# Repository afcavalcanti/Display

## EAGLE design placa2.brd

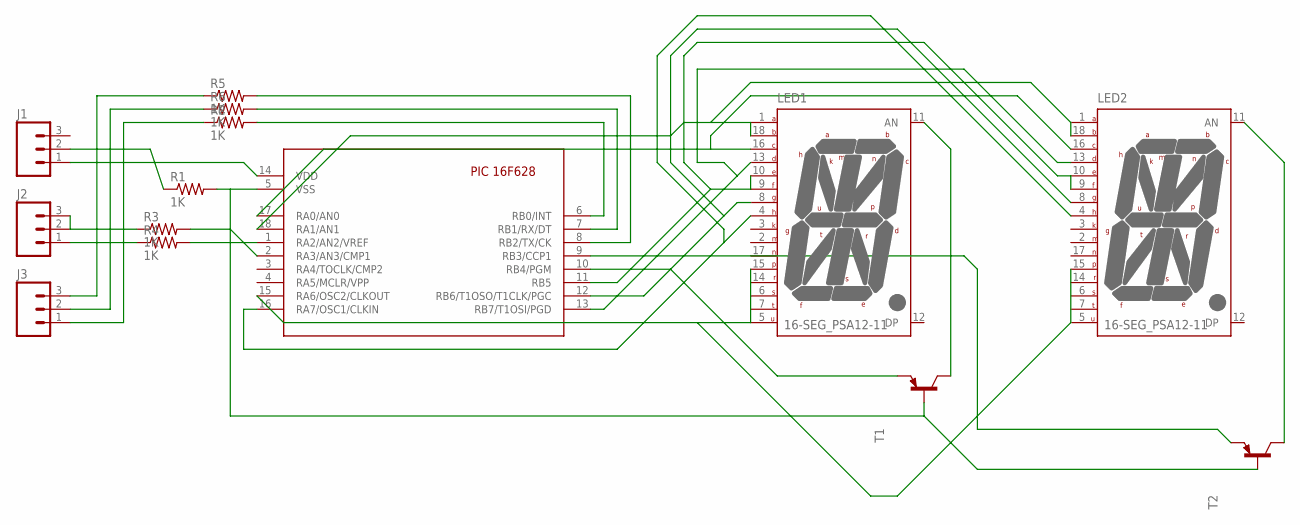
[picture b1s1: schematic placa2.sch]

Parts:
J1, J2, J3: M03-SCREW-5MM; SCREWTERMINAL-5MM-3
LED1, LED2: 16-SEG_PSA12-11; PSA12-11
R1, R2, R3, R4, R5, R6: 1K; AXIAL-0.3
T1, T2: BC558B-PNP-TO92-EBC; TO92-EBC
U$1: 16F628; PIC16F628-18-LEAD-PDIP

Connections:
unnamed: J1.1, U$1.14 (VDD)
unnamed: J1.2, R1.P$1 (1)
unnamed: J2.1, R4.P$1 (1)
unnamed: R1.P$2 (2), T1.B, T2.B, U$1.5 (VSS)
unnamed: J2.3, R3.P$1 (1)
unnamed: J3.3, R5.P$1 (1)
unnamed: R2.P$2 (2), U$1.6 (RB0/INT)
unnamed: R6.P$2 (2), U$1.7 (RB1/RX/DT)
unnamed: R5.P$2 (2), U$1.8 (RB2/TX/CK)
unnamed: LED1.1 (A), LED1.18 (B), LED2.1 (A), LED2.18 (B), U$1.18 (RA1/AN1)
unnamed: LED1.4 (H), LED2.4 (H), U$1.16 (RA7/OSC1/CLKIN)
unnamed: LED1.11 (AN), T1.C
unnamed: LED1.16 (C), LED2.16 (C), U$1.17 (RA0/AN0)
unnamed: J3.2, R6.P$1 (1)
unnamed: LED2.11 (AN), T2.C
unnamed: J3.1, R2.P$1 (1)
unnamed: LED1.13 (D), LED2.13 (D), U$1.13 (RB7/T1OSI/PGD)
unnamed: LED1.8 (G), LED2.8 (G), U$1.12 (RB6/T1OSO/T1CLK/PGC)
unnamed: T1.E, U$1.10 (RB4/PGM)
unnamed: T2.E, U$1.9 (RB3/CCP1)
unnamed: R3.P$2 (2), U$1.2 (RA3/AN3/CMP1)
unnamed: LED1.5 (U), LED1.15, LED2.5 (U), LED2.15, U$1.15 (RA6/OSC2/CLKOUT)
unnamed: LED1.9 (F), LED1.10 (E), LED2.9 (F), LED2.10 (E), U$1.11 (RB5)
unnamed: R4.P$2 (2), U$1.1 (RA2/AN2/VREF)

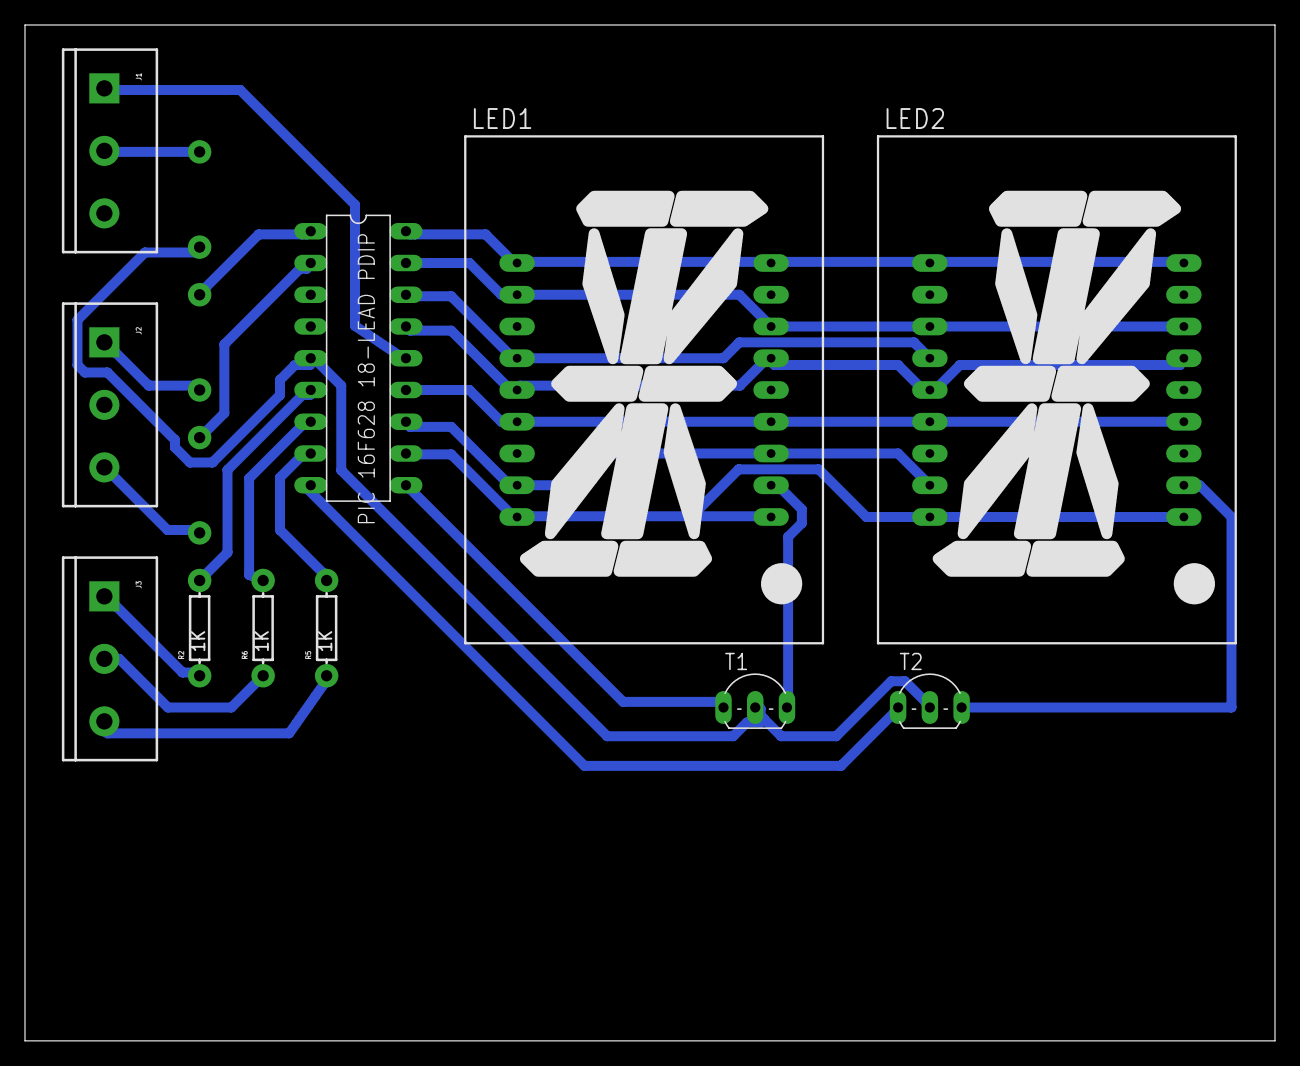
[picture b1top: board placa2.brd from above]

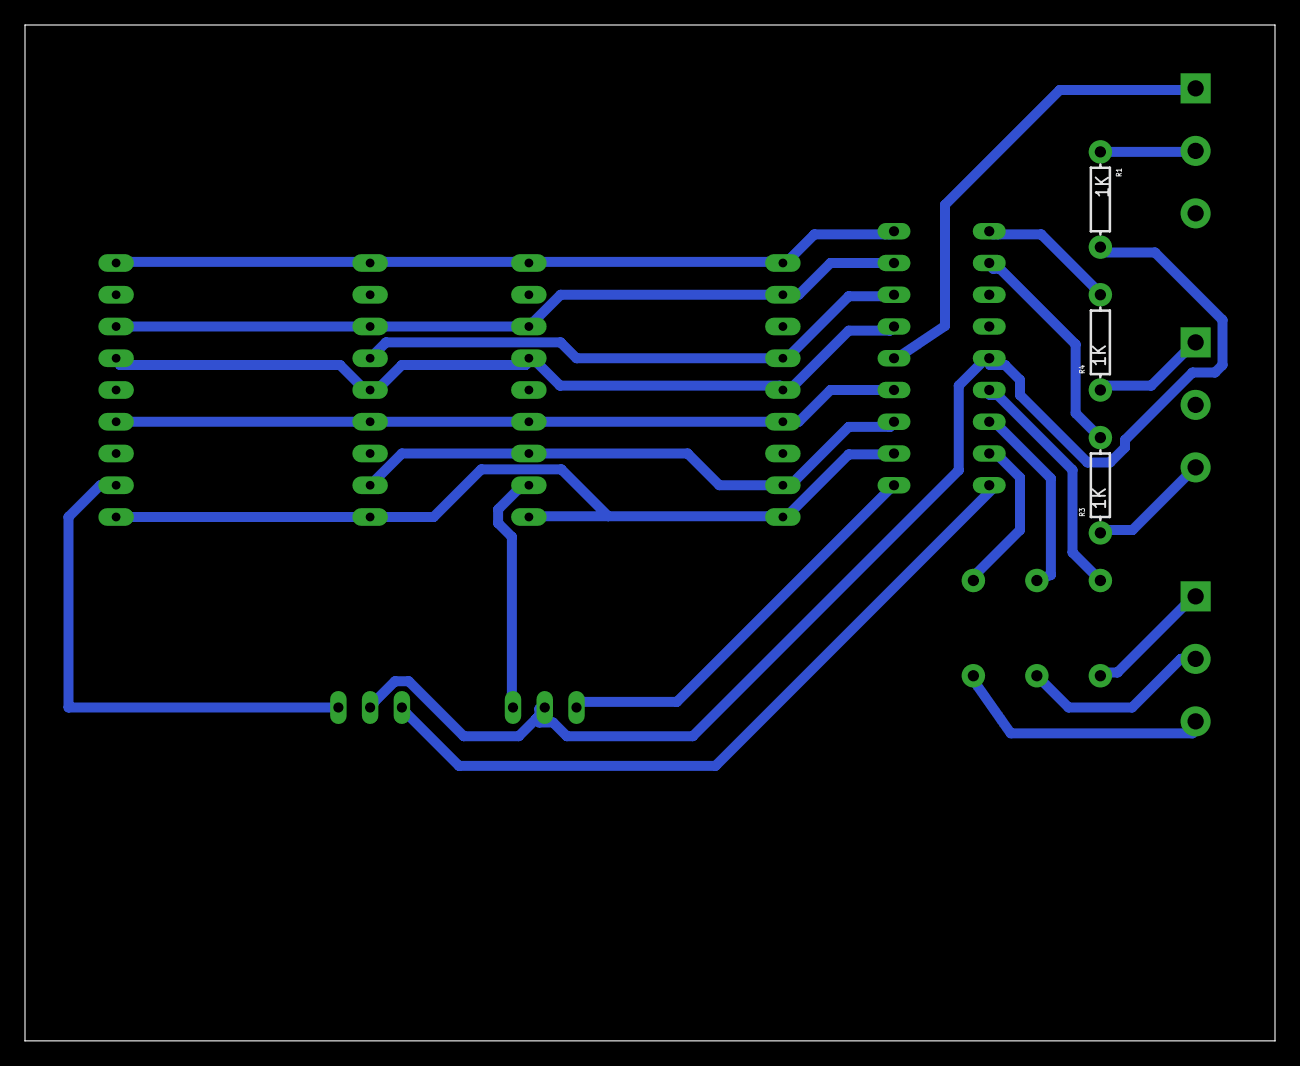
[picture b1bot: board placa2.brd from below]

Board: 2 copper layers, 100.0 x 81.3 mm, 14 parts (3 on the bottom side), 24 nets.

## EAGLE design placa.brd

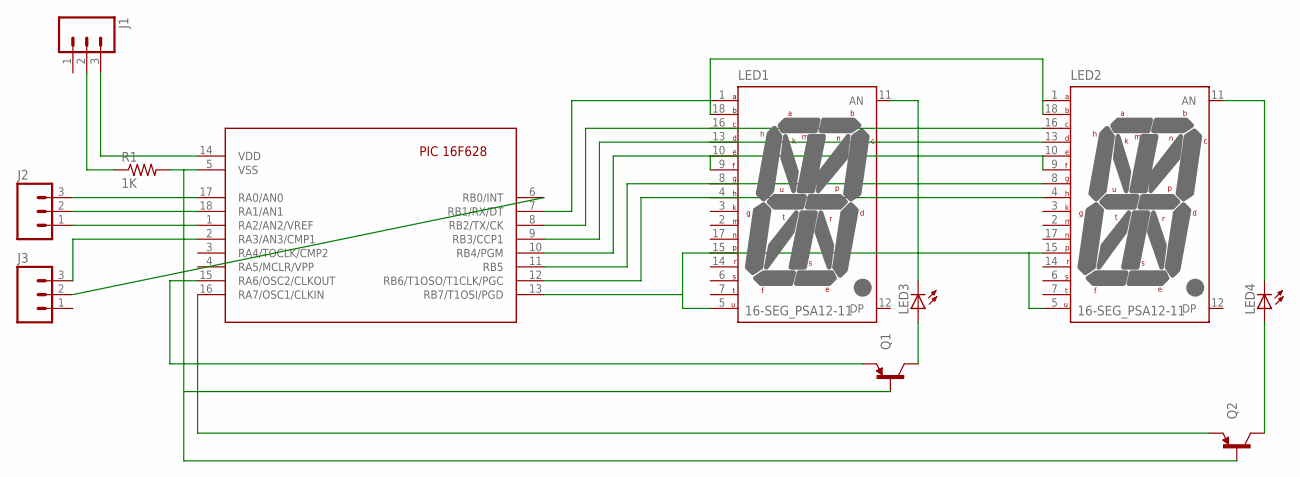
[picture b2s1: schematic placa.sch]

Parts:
J1, J2, J3: M03-SCREW-5MM; SCREWTERMINAL-5MM-3
LED1, LED2: 16-SEG_PSA12-11; PSA12-11
LED3, LED4: LED3MM
Q1, Q2: TRANSISTOR_PNPTO92; TO-92
R1: 1K; AXIAL-0.3
U$1: 16F628; PIC16F628-18-LEAD-PDIP

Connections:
unnamed: LED1.5 (U), LED1.15, LED2.5 (U), LED2.15, U$1.13 (RB7/T1OSI/PGD)
unnamed: LED1.1 (A), LED1.18 (B), LED2.1 (A), LED2.18 (B), U$1.7 (RB1/RX/DT)
unnamed: LED1.16 (C), LED2.16 (C), U$1.8 (RB2/TX/CK)
unnamed: LED1.13 (D), LED2.13 (D), U$1.9 (RB3/CCP1)
unnamed: LED1.9 (F), LED1.10 (E), LED2.9 (F), LED2.10 (E), U$1.10 (RB4/PGM)
unnamed: LED1.8 (G), LED2.8 (G), U$1.11 (RB5)
unnamed: LED1.4 (H), LED2.4 (H), U$1.12 (RB6/T1OSO/T1CLK/PGC)
unnamed: Q1.1 (E), U$1.15 (RA6/OSC2/CLKOUT)
unnamed: Q2.1 (E), U$1.16 (RA7/OSC1/CLKIN)
unnamed: J1.3, U$1.14 (VDD)
unnamed: J1.2, R1.P$1 (1)
unnamed: Q1.2 (B), Q2.2 (B), R1.P$2 (2), U$1.5 (VSS)
unnamed: J2.3, U$1.17 (RA0/AN0)
unnamed: J2.2, U$1.18 (RA1/AN1)
unnamed: J2.1, U$1.1 (RA2/AN2/VREF)
unnamed: J3.3, U$1.2 (RA3/AN3/CMP1)
unnamed: LED1.11 (AN), LED3.K (C)
unnamed: LED2.11 (AN), LED4.K (C)
unnamed: LED3.A, Q1.3 (C)
unnamed: LED4.A, Q2.3 (C)
unnamed: J3.2, U$1.6 (RB0/INT)

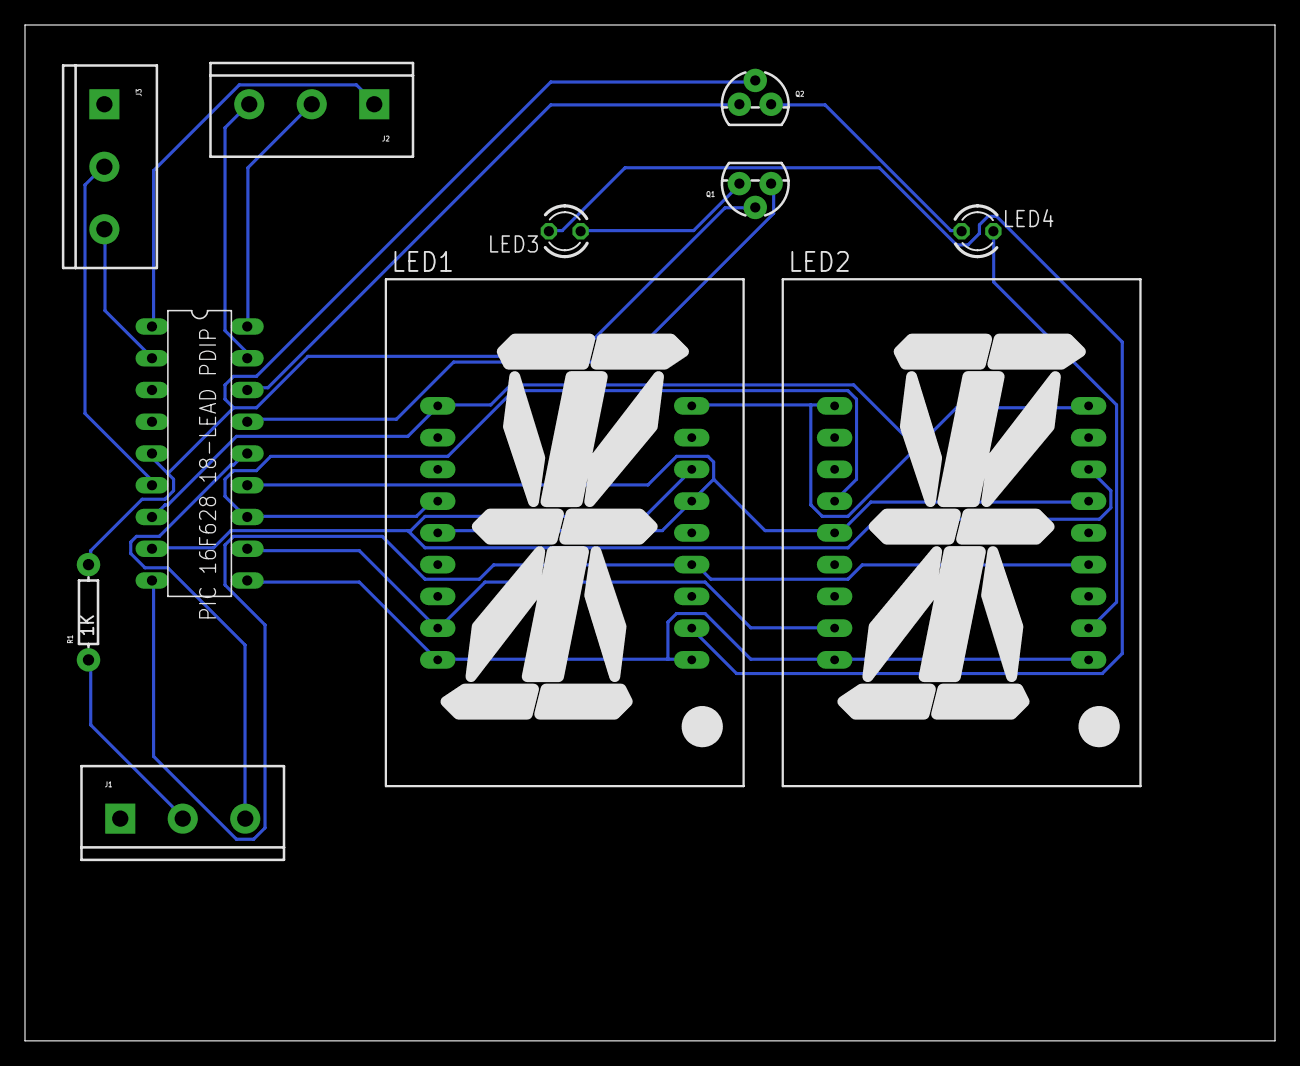
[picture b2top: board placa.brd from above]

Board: 2 copper layers, 100.0 x 81.3 mm, 11 parts (0 on the bottom side), 21 nets.

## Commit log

2016-08-26 modified: display.mcs 40044d.pdf
2016-08-26 new file: 40044d.pdf
2016-08-28 modified: Last Loaded display.DBK modified: display.DSN modified: display.PWI modified: display.c deleted: display.cof deleted: display.err deleted: display.esym deleted: display.hex deleted: display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
2016-08-28 falta desenhar a placa
2016-09-06 feito
2016-09-08 falta editar o arquvo C

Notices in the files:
parts and their libraries:
SparkFun-Connectors: Licensing: Creative Commons ShareAlike 4.0 International - https://creativecommons.org/licenses/by-sa/4.0
